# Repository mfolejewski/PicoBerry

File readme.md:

# PicoBerry - miniature Raspberry Pi CM4 carrier board with full 40-pin GPIO header

## Description

PicoBerry is a tiny Raspberry Pi CM4 carrier board, which has technical specification, as following:
- USB-C for power supply (5VDC/3A),
- full 40-pin GPIO header for connecting HAT boards,
- 2x user LEDs (green/red),
- support only CM4 versions (with eMMC onboard, CM4 Lite are not supported),
- standard ACT/PWR LEDs,
- 2-layer PCB, 20x70mm,
- fully open source project (OSHW).

You can connect to the CM4 module standard HAT boards, such as LCD screens (with SPI or DPI interfaces), audio DAC boards, RS232/485 or CAN interfaces, and many more...

Here you can find:
- \photos: a few pictures of the assembled PCB boards and design
- \manufacturing files: all the production files for ordering PCB and assembly at JLCPCB (Gerber files, Pick & Place, BOM, etc.)
- \source files: source files in KiCad and Altium Designer format

## License

Project published as Open Source Hardware (OSHW) under CERN OHL v1.2 (Open Hardware Licence).

Project has been certified as Open Source Hardware by the Open Source Hardware Association (OSHWA).

UID is: PL000010

https://certification.oshwa.org/pl000010.html

## Press release:

[Tom's Hardware](https://www.tomshardware.com/news/picoberry-raspberry-pi-4-compute-module-4-carrier-board)

[CNX Software](https://www.cnx-software.com/2022/10/24/miniature-raspberry-pi-cm4-carrier-board-usb-c-port-40-pin-gpio-header)

[NotebookCheck (EN)](https://www.notebookcheck.net/PicoBerry-Raspberry-Pi-Compute-Module-4-carrier-board-arrives-with-40-pin-GPIO-header-and-USB-Type-C-connectivity.664512.0.html)

[NotebookCheck (DE)](https://www.notebookcheck.com/PicoBerry-Besonders-kompaktes-Carrier-Board-fuer-das-Raspberry-Pi-CM4-ist-Open-Source.663859.0.html)

[NotebookCheck (PL)](https://www.notebookcheck.pl/PicoBerry-Raspberry-Plyta-nosna-Pi-Compute-Module-4-przybywa-z-40-pinowym-headerem-GPIO-i-lacznoscia-USB-Type-C.664668.0.html)

[Elektroda.pl (PL)](https://www.elektroda.pl/rtvforum/topic3928796.html)

[LinuxDevices](https://twitter.com/linuxdevices/status/1584419970343395328)

[Tux Machines](http://news.tuxmachines.org/n/2022/10/25/PicoBerry_Carrier_Board_for_the_Raspberry_Pi_CM_4_Build_one_for.shtml)

[Jeff Geerling](https://pipci.jeffgeerling.com/boards_cm/mirkos-picoberry-carrier-board.html)

[hackaday.io](https://hackaday.io/project/182747-picoberry-tiny-cm4-carrier-board)

...and much more:

https://twitter.com/search?q=picoberry&src=typed_query&f=live

https://www.google.com/search?q=picoberry+cm4&oq=picoberry+cm4

## Photos

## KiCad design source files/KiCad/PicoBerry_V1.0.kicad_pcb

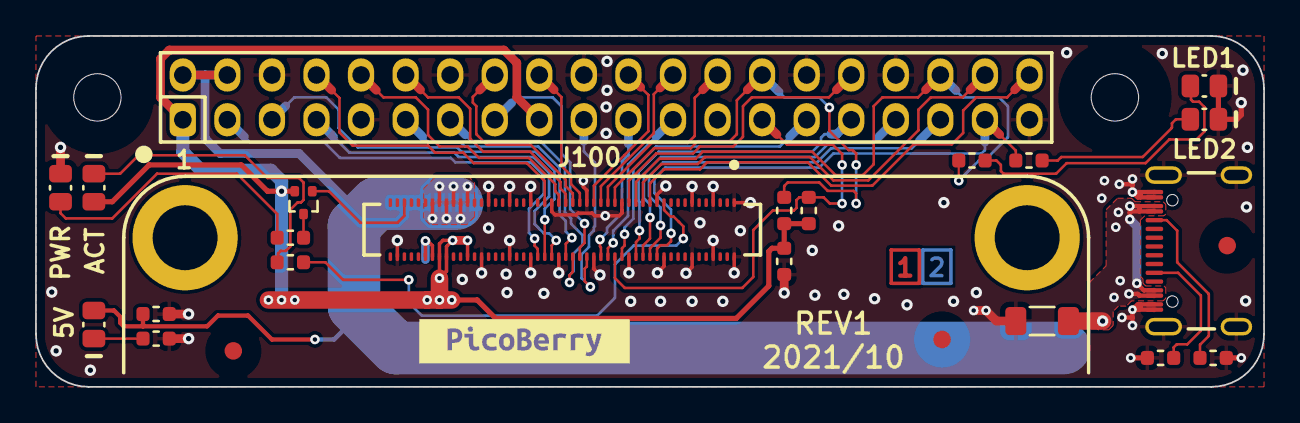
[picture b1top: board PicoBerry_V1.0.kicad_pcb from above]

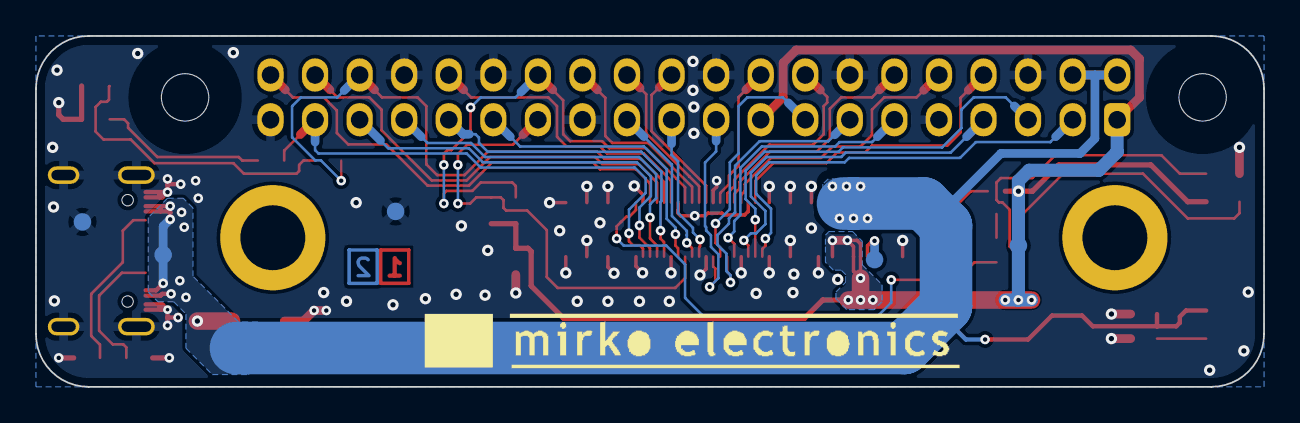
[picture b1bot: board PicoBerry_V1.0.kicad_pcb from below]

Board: 2 copper layers, 70.0 x 20.0 mm, 36 parts (5 on the bottom side), 42 nets.

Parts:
C900: 100uF/6V3; CAP_1206_R
FID950, FID954, FID955: Fiducial; PCB_FID_RND_100x300
J100: 40pin (2x20pin); CON_HDR_P254_2X20M_STR
J103: Mezzanine, 100pin, 3.0mm; PCB_BLANK_COMP_SMD
J200: U262-161N-4BVC11; _!MirFol_lib_MirFol_lib.PcbLib_CON_XKB_U262-161N-4BVC11
LED100, LED801: Red; LED_0805_RED_R
LED101, LED800, LED900: Green; LED_0805_GRN_R
MECH952, MECH953: M2.5, L = 3.0mm; PCB_WRT_9774030151
MH950, MH953: H270_C600; _2020-11-04_MirFol_lib.PcbLib_PCB_MH_H270_C600
MOD100: RPi CM4 Module; _CM4_PicoBerry_lib_MirFol_lib_Modules.PcbLib_MOD_RPI_CM4_P4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
PCB950: PCB_LAYER_STACKUP; _Biblioteki_MirFol_nowe_Pineberry_Lib.PcbLib_PCB_STACKUP-2L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
Q902: DTA143ZE; PKG_SOT523_SC75_SOT416_P100_R
R101, R102, R107, R805, R907: 2k; RES_0603_R
R105: 2k; _!MirFol_lib_MirFol_db_local.DbLib_RESISTOR$_RES_0603_R
R106: 15k; _!MirFol_lib_MirFol_db_local.DbLib_RESISTOR$_RES_0603_R
R201, R203: 5k1; _!MirFol_lib_MirFol_db_local.DbLib_RESISTOR$_RES_0603_R
R804, R901: 15k; RES_0603_R
TP119, TP120, TP914, TP915, TP916: ICT; PCB_TP_ICT_100
kibuzzard-634662D7: G***; kibuzzard-634662D7

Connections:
+1V8: MOD100.88 (+1.8V(Output)), MOD100.90 (+1.8V(Output)), TP120.1
+3V3: J100.1, J100.17, LED101.2, MOD100.78 (GPIO_VREF), MOD100.84 (+3.3V(Output)), MOD100.86 (+3.3V(Output)), Q902.2 (E), R101.2, R102.2, R107.2, TP119.1
+5V: C900.2, J100.2, J100.4, J200.A4 (VBUS), J200.A9 (VBUS), J200.B4 (VBUS), J200.B9 (VBUS), LED900.2, MOD100.77 (+5V(Input)), MOD100.79 (+5V(Input)), MOD100.81 (+5V(Input)), MOD100.83 (+5V(Input)), MOD100.85 (+5V(Input)), MOD100.87 (+5V(Input)), R907.2, TP914.1
/CM4/CM_GPIO2: J100.3, MOD100.58 (GPIO2)
/CM4/CM_GPIO3: J100.5, MOD100.56 (GPIO3)
/CM4/CM_GPIO4: J100.7, MOD100.54 (GPIO4)
/CM4/CM_GPIO5: J100.29, MOD100.34 (GPIO5)
/CM4/CM_GPIO6: J100.31, MOD100.30 (GPIO6)
/CM4/CM_GPIO7: J100.26, MOD100.37 (GPIO7)
/CM4/CM_GPIO8: J100.24, MOD100.39 (GPIO8)
/CM4/CM_GPIO9: J100.21, MOD100.40 (GPIO9)
/CM4/CM_GPIO10: J100.19, MOD100.44 (GPIO10)
/CM4/CM_GPIO11: J100.23, MOD100.38 (GPIO11)
/CM4/CM_GPIO12: J100.32, MOD100.31 (GPIO12)
/CM4/CM_GPIO13: J100.33, MOD100.28 (GPIO13)
/CM4/CM_GPIO14: J100.8, MOD100.55 (GPIO14)
/CM4/CM_GPIO15: J100.10, MOD100.51 (GPIO15)
/CM4/CM_GPIO16: J100.36, MOD100.29 (GPIO16), R804.1
/CM4/CM_GPIO17: J100.11, MOD100.50 (GPIO17)
/CM4/CM_GPIO18: J100.12, MOD100.49 (GPIO18)
/CM4/CM_GPIO19: J100.35, MOD100.26 (GPIO19)
/CM4/CM_GPIO20: J100.38, MOD100.27 (GPIO20)
/CM4/CM_GPIO21: J100.40, MOD100.25 (GPIO21)
/CM4/CM_GPIO22: J100.15, MOD100.46 (GPIO22)
/CM4/CM_GPIO23: J100.16, MOD100.47 (GPIO23)
/CM4/CM_GPIO24: J100.18, MOD100.45 (GPIO24)
/CM4/CM_GPIO25: J100.22, MOD100.41 (GPIO25)
/CM4/CM_GPIO26: J100.37, MOD100.24 (GPIO26), R805.1
/CM4/CM_GPIO27: J100.13, MOD100.48 (GPIO27)
/CM4/CM_ID_SC: J100.28, MOD100.35 (ID_SC), R102.1
/CM4/CM_ID_SD: J100.27, MOD100.36 (ID_SD), R101.1
/CM4/CM_nACT: MOD100.21 (Pi_LED_nActivity), R106.1
/CM4/CM_nPWR: MOD100.95 (Pi_LED_nPWR), Q902.1 (B)
/PWR/USB_CC1: J200.A5 (CC1), R203.1
/PWR/USB_CC2: J200.B5 (CC2), R201.1
GND: C900.1, J100.6, J100.9, J100.14, J100.20, J100.25, J100.30, J100.34, J100.39, J200.A1 (GND), J200.A12 (GND), J200.B1 (GND), J200.B12 (GND), J200.SH (SHIELD), LED100.1, LED800.1, LED801.1, MOD100.1 (GND), MOD100.2 (GND), MOD100.7 (GND), MOD100.8 (GND), MOD100.13 (GND), MOD100.14 (GND), MOD100.22 (GND), MOD100.23 (GND), MOD100.32 (GND), MOD100.33 (GND), MOD100.42 (GND), MOD100.43 (GND), MOD100.52 (GND), MOD100.53 (GND), MOD100.59 (GND), MOD100.60 (GND), MOD100.65 (GND), MOD100.66 (GND), MOD100.71 (GND), MOD100.74 (GND), MOD100.98 (GND), R107.1, R201.2, R203.2, R901.2, R907.1, TP915.1, TP916.1
unnamed: LED100.2, R105.1
unnamed: LED101.1, R106.2
unnamed: LED800.2, R804.2
unnamed: LED801.2, R805.2
unnamed: LED900.1, R901.1
unnamed: Q902.3 (C), R105.2

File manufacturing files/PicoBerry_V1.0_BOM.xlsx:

Comment | Designator | Value | Footprint | MPN
100uF/6V3 | C900 | 100uF/6V3 | CAP_1206_R | GENERIC
40pin (2x20pin) | J100 | 40pin (2x20pin) | CON_HDR_P254_2X20M_STR | GENERIC
Mezzanine, 100pin, 3.0mm | J103 | Mezzanine, 100pin, 3.0mm | PCB_BLANK_COMP_SMD | DF40HC(3.0)-100DS-0.4V
U262-161N-4BVC11 | J200 | U262-161N-4BVC11 | CON_XKB_U262-161N-4BVC11 | U262-161N-4BVC11
Red | LED100, LED801 | Red | LED_0805_RED_R | NCD0805R1
Green | LED101, LED800, LED900 | Green | LED_0805_GRN_R | NCD0805G1
M2.5, L = 3.0mm | MECH952, MECH953 | M2.5, L = 3.0mm | PCB_WRT_9774030151 | 977 403 015 1
RPi CM4 Module | MOD100 | RPi CM4 Module | MOD_RPI_CM4_P40_C300_CON1 | CM4 Module
PCB BARE BOARD | PCB1 | PCB BARE BOARD |  | N/A
DTA143ZE | Q902 | DTA143ZE | PKG_SOT523_SC75_SOT416_P100_R | DTA143ZET1G
2k | R101, R102, R105, R107, R805, R907 | 2k | RES_0603_R | TBD
15k | R106, R804, R901 | 15k | RES_0603_R | TBD
5k1 | R201, R203 | 5k1 | RES_0603_R | TBD
M2.5 | SCR950, SCR951 | M2.5 |  | M2.5 screw

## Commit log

2022-10-23 Create Altium
2022-10-27 Update readme.md
    added press release
